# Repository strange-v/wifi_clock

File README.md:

# WiFi Clock
One more WiFi clock based on DS1339U and ESP8266. Requires 12V 1.5A power source.

## Functionality
* 24 hours time format
* Automatic time sync (NTP server and interval can be configured)
* Auto brightness
* DST support
* Display options (on/off leading zero, on/off column blinking, do not blink in a specific period of time)
* Over-the-Air update

## Main components
- ESP8266 - microcontroller 
- DS1339U - real time clock
- PCA9685 x 2 - LED controller
- BH1750FVI-TR - light sensor
- MT2492 - step-down  converter
- LM1117IMP-3.3 - voltage regulator

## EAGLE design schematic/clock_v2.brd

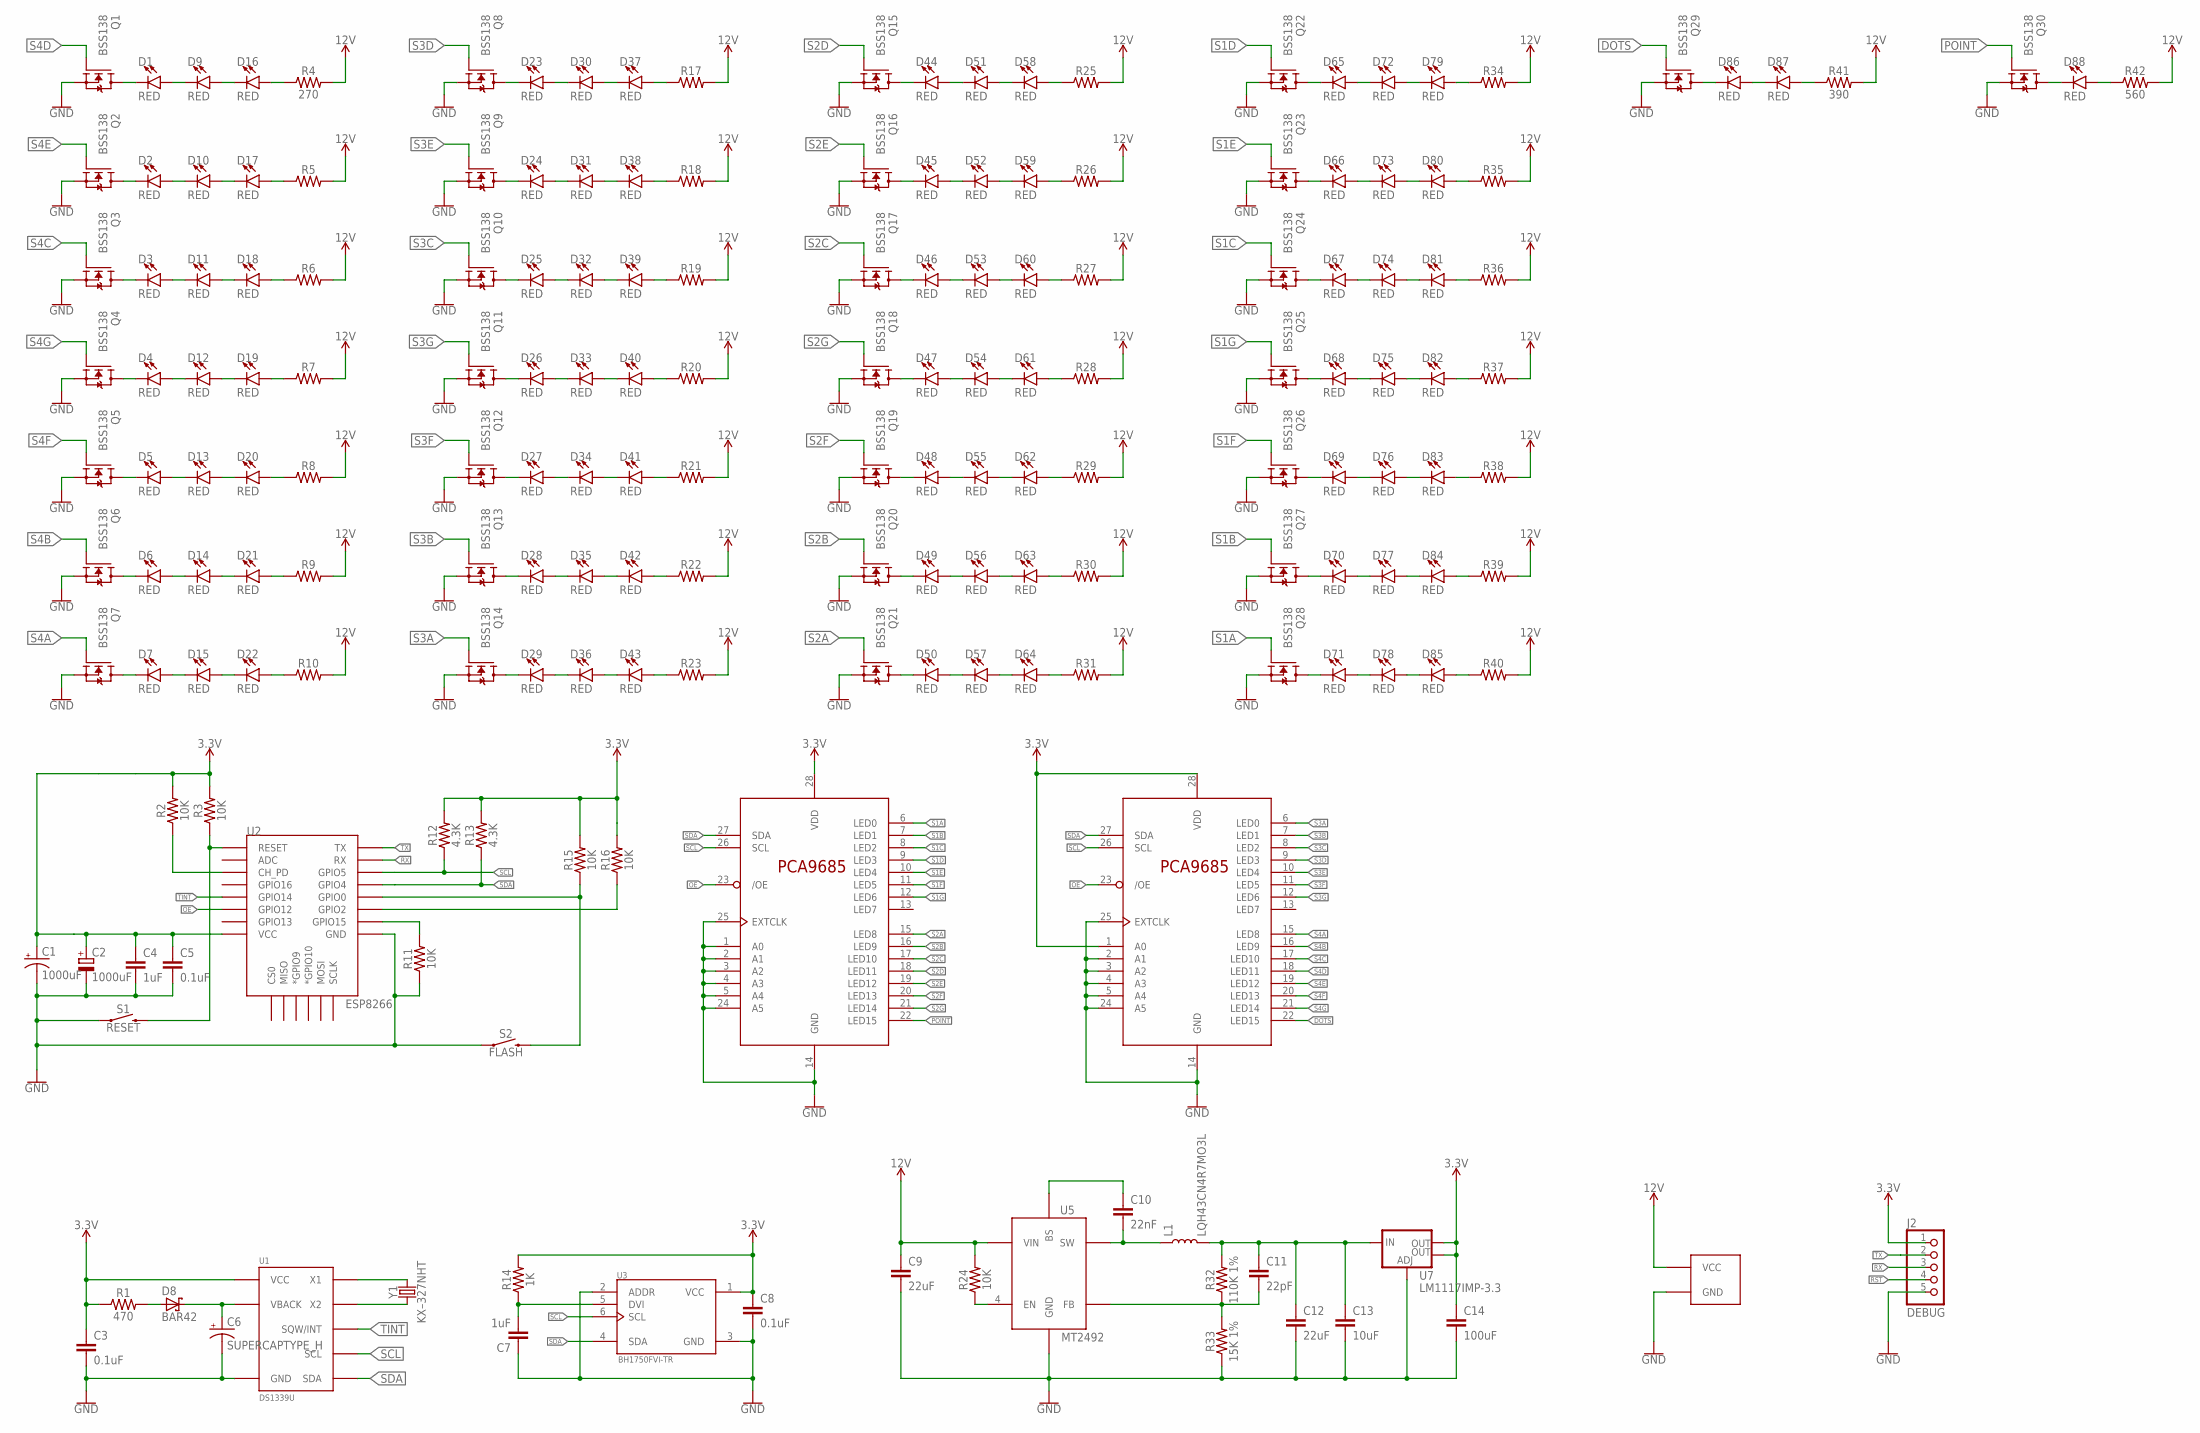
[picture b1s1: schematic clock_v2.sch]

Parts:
C1: 1000uF; CAP_8X11.5_P-3.5
C2: 1000uF; D/7343-31R
C3, C5, C8: 0.1uF; 1206
C4, C7: 1uF; 1206
C6: SUPERCAPTYPE_H; IONISTOR_TYPE_H
C9, C12: 22uF; 1206
C10: 22nF; 1206
C11: 22pF; 1206
C13: 10uF; 1206
C14: 100uF; C/6032-28R
D1, D2, D3, D4, D5, D6, D7, D9, D10, D11, D12, D13, D14, D15, D16, D17, D18, D19, D20, D21, D22, D23, D24, D25, D26, D27, D28, D29, D30, D31, D32, D33, D34, D35, D36, D37, D38, D39, D40, D41, D42, D43, D44, D45, D46, D47, D48, D49, D50, D51, D52, D53, D54, D55, D56, D57, D58, D59, D60, D61, D62, D63, D64, D65, D66, D67, D68, D69, D70, D71, D72, D73, D74, D75, D76, D77, D78, D79, D80, D81, D82, D83, D84, D85, D86, D87, D88: RED; LED-1206
D8: BAR42; SOT23
J1: POWER_SMD5.08; POWER_SMD_5.08
J2: DEBUG; ESP8266_DEBUG
L1: LQH43CN4R7MO3L; C1812
Q1, Q2, Q3, Q4, Q5, Q6, Q7, Q8, Q9, Q10, Q11, Q12, Q13, Q14, Q15, Q16, Q17, Q18, Q19, Q20, Q21, Q22, Q23, Q24, Q25, Q26, Q27, Q28, Q29, Q30: BSS138; SOT23
R1: 470; 1206
R2, R3, R11, R15, R16, R24: 10K; 1206
R4: 270; 1206
R5, R6, R7, R8, R9, R10, R17, R18, R19, R20, R21, R22, R23, R25, R26, R27, R28, R29, R30, R31, R34, R35, R36, R37, R38, R39, R40: 1206
R12, R13: 4.3K; 1206
R14: 1K; 1206
R32: 110K 1%; 1206
R33: 15K 1%; 1206
R41: 390; 1206
R42: 560; 1206
S1: RESET; TACTILE_SWITCH_SMD_5.2MM
S2: FLASH; TACTILE_SWITCH_SMD_5.2MM
U1: DS1339U
U2: ESP8266; ESP12E-SMD
U3: BH1750FVI-TR; SOTFL50P300X75-6N
U4, U6: PCA9685PW; TSSOP28
U5: MT2492; SOT23-6
U7: LM1117IMP-3.3; SOT223
Y1: KX–327NHT; QSMD3.2X1.5

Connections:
3.3V: C1.+, C2.+, C3.1, C4.1, C5.1, C8.1, C14.+ (1), J2.1, R1.1, R2.2, R3.2, R12.2, R13.2, R14.2, R15.2, R16.2, U1.8 (VCC), U2.VCC, U3.1 (VCC), U4.28 (VDD), U6.1 (A0), U6.28 (VDD), U7.2 (OUT), U7.4 (OUT)
12V: C9.1, J1.VCC, R4.2, R5.2, R6.2, R7.2, R8.2, R9.2, R10.2, R17.2, R18.2, R19.2, R20.2, R21.2, R22.2, R23.2, R24.2, R25.2, R26.2, R27.2, R28.2, R29.2, R30.2, R31.2, R34.2, R35.2, R36.2, R37.2, R38.2, R39.2, R40.2, R41.2, R42.2, U5.5 (VIN)
DOTS: Q29.1 (G), U6.22 (LED15)
FLASH: R15.1, S2.3 (2), S2.4 (2), U2.GPIO0
GND: C1.-, C2.-, C3.2, C4.2, C5.2, C6.GND (-), C7.1, C8.2, C9.2, C12.2, C13.2, C14.- (2), J1.GND, J2.5, Q1.2 (S), Q2.2 (S), Q3.2 (S), Q4.2 (S), Q5.2 (S), Q6.2 (S), Q7.2 (S), Q8.2 (S), Q9.2 (S), Q10.2 (S), Q11.2 (S), Q12.2 (S), Q13.2 (S), Q14.2 (S), Q15.2 (S), Q16.2 (S), Q17.2 (S), Q18.2 (S), Q19.2 (S), Q20.2 (S), Q21.2 (S), Q22.2 (S), Q23.2 (S), Q24.2 (S), Q25.2 (S), Q26.2 (S), Q27.2 (S), Q28.2 (S), Q29.2 (S), Q30.2 (S), R11.1, R33.1, S1.1, S1.2 (1), S2.1, S2.2 (1), U1.4 (GND), U2.GND, U3.2 (ADDR), U3.3 (GND), U4.1 (A0), U4.2 (A1), U4.3 (A2), U4.4 (A3), U4.5 (A4), U4.14 (GND), U4.24 (A5), U4.25 (EXTCLK), U5.2 (GND), U6.2 (A1), U6.3 (A2), U6.4 (A3), U6.5 (A4), U6.14 (GND), U6.24 (A5), U6.25 (EXTCLK), U7.1 (ADJ)
unnamed: D1.C, Q1.3 (D)
unnamed: D1.A, D9.C
unnamed: D2.C, Q2.3 (D)
unnamed: D2.A, D10.C
unnamed: D3.C, Q3.3 (D)
unnamed: D3.A, D11.C
unnamed: D11.A, D18.C
unnamed: D18.A, R6.1
unnamed: D4.C, Q4.3 (D)
unnamed: D4.A, D12.C
unnamed: D12.A, D19.C
unnamed: D19.A, R7.1
unnamed: D7.C, Q7.3 (D)
unnamed: D7.A, D15.C
unnamed: D50.C, Q21.3 (D)
unnamed: D23.C, Q8.3 (D)
unnamed: D23.A, D30.C
unnamed: D30.A, D37.C
unnamed: D37.A, R17.1
unnamed: D24.C, Q9.3 (D)
unnamed: D24.A, D31.C
unnamed: D31.A, D38.C
unnamed: D38.A, R18.1
unnamed: D25.C, Q10.3 (D)
unnamed: D25.A, D32.C
unnamed: D32.A, D39.C
unnamed: D39.A, R19.1
unnamed: D27.C, Q12.3 (D)
unnamed: D50.A, D57.C
unnamed: D57.A, D64.C
unnamed: D49.C, Q20.3 (D)
unnamed: D49.A, D56.C
unnamed: D56.A, D63.C
unnamed: D48.C, Q19.3 (D)
unnamed: D48.A, D55.C
unnamed: D55.A, D62.C
unnamed: D47.C, Q18.3 (D)
unnamed: D47.A, D54.C
unnamed: D54.A, D61.C
unnamed: D46.C, Q17.3 (D)
unnamed: D46.A, D53.C
unnamed: D53.A, D60.C
unnamed: D44.C, Q15.3 (D)
unnamed: D44.A, D51.C
unnamed: D51.A, D58.C
unnamed: D52.A, D59.C
unnamed: D45.A, D52.C
unnamed: D45.C, Q16.3 (D)
unnamed: D64.A, R31.1
unnamed: D63.A, R30.1
unnamed: D62.A, R29.1
unnamed: D61.A, R28.1
unnamed: D60.A, R27.1
unnamed: D59.A, R26.1
unnamed: D58.A, R25.1
unnamed: D65.C, Q22.3 (D)
unnamed: D86.A, D87.C
unnamed: D86.C, Q29.3 (D)
unnamed: D9.A, D16.C
unnamed: D16.A, R4.1
unnamed: D10.A, D17.C
unnamed: D17.A, R5.1
unnamed: D15.A, D22.C
unnamed: D22.A, R10.1
unnamed: D6.C, Q6.3 (D)
unnamed: D6.A, D14.C
unnamed: D14.A, D21.C
unnamed: D21.A, R9.1
unnamed: D5.C, Q5.3 (D)
unnamed: D5.A, D13.C
unnamed: D13.A, D20.C
unnamed: D20.A, R8.1
unnamed: D88.C, Q30.3 (D)
unnamed: D27.A, D34.C
unnamed: D87.A, R41.1
unnamed: D88.A, R42.1
unnamed: D34.A, D41.C
unnamed: D41.A, R21.1
unnamed: D28.C, Q13.3 (D)
unnamed: D28.A, D35.C
unnamed: D35.A, D42.C
unnamed: D42.A, R22.1
unnamed: D29.C, Q14.3 (D)
unnamed: D29.A, D36.C
unnamed: D36.A, D43.C
unnamed: D43.A, R23.1
unnamed: D26.C, Q11.3 (D)
unnamed: D26.A, D33.C
unnamed: D33.A, D40.C
unnamed: D40.A, R20.1
unnamed: D65.A, D72.C
unnamed: D72.A, D79.C
unnamed: D79.A, R34.1
unnamed: D66.C, Q23.3 (D)
unnamed: D66.A, D73.C
unnamed: D73.A, D80.C
unnamed: D80.A, R35.1
unnamed: D67.C, Q24.3 (D)
unnamed: D67.A, D74.C
unnamed: D74.A, D81.C
unnamed: D81.A, R36.1
unnamed: D82.A, R37.1
unnamed: D75.A, D82.C
unnamed: D68.A, D75.C
unnamed: D68.C, Q25.3 (D)
unnamed: D69.C, Q26.3 (D)
unnamed: D69.A, D76.C
unnamed: D76.A, D83.C
unnamed: D83.A, R38.1
unnamed: D84.A, R39.1
unnamed: D77.A, D84.C
unnamed: D70.A, D77.C
unnamed: D70.C, Q27.3 (D)
unnamed: D71.C, Q28.3 (D)
unnamed: D71.A, D78.C
unnamed: D78.A, D85.C
unnamed: D85.A, R40.1
unnamed: C6.VCC (+), D8.3 (C), U1.3 (VBACK)
unnamed: C7.2, R14.1, U3.5 (DVI)
unnamed: D8.1 (A), R1.2
unnamed: U1.1 (X1), Y1.2
unnamed: U1.2 (X2), Y1.1
unnamed: R11.2, U2.GPIO15
unnamed: R2.1, U2.CH_PD
unnamed: R16.1, U2.GPIO2
unnamed: R24.1, U5.4 (EN)
unnamed: C10.1, U5.1 (BS)
unnamed: C10.2, L1.1, U5.6 (SW)
unnamed: C11.1, C12.1, C13.1, L1.2, R32.2, U7.3 (IN)
unnamed: C11.2, R32.1, R33.2, U5.3 (FB)
OE: U2.GPIO12, U4.23 (/OE), U6.23 (/OE)
POINT: Q30.1 (G), U4.22 (LED15)
RST: J2.4, R3.1, S1.3 (2), S1.4 (2), U2.RESET
RX: J2.3, U2.RXD0 (RX)
S1A: Q28.1 (G), U4.6 (LED0)
S1B: Q27.1 (G), U4.7 (LED1)
S1C: Q24.1 (G), U4.8 (LED2)
S1D: Q22.1 (G), U4.9 (LED3)
S1E: Q23.1 (G), U4.10 (LED4)
S1F: Q26.1 (G), U4.11 (LED5)
S1G: Q25.1 (G), U4.12 (LED6)
S2A: Q21.1 (G), U4.15 (LED8)
S2B: Q20.1 (G), U4.16 (LED9)
S2C: Q17.1 (G), U4.17 (LED10)
S2D: Q15.1 (G), U4.18 (LED11)
S2E: Q16.1 (G), U4.19 (LED12)
S2F: Q19.1 (G), U4.20 (LED13)
S2G: Q18.1 (G), U4.21 (LED14)
S3A: Q14.1 (G), U6.6 (LED0)
S3B: Q13.1 (G), U6.7 (LED1)
S3C: Q10.1 (G), U6.8 (LED2)
S3D: Q8.1 (G), U6.9 (LED3)
S3E: Q9.1 (G), U6.10 (LED4)
S3F: Q12.1 (G), U6.11 (LED5)
S3G: Q11.1 (G), U6.12 (LED6)
S4A: Q7.1 (G), U6.15 (LED8)
S4B: Q6.1 (G), U6.16 (LED9)
S4C: Q3.1 (G), U6.17 (LED10)
S4D: Q1.1 (G), U6.18 (LED11)
S4E: Q2.1 (G), U6.19 (LED12)
S4F: Q5.1 (G), U6.20 (LED13)
S4G: Q4.1 (G), U6.21 (LED14)
SCL: R12.1, U1.6 (SCL), U2.GPIO5, U3.6 (SCL), U4.26 (SCL), U6.26 (SCL)
SDA: R13.1, U1.5 (SDA), U2.GPIO4, U3.4 (SDA), U4.27 (SDA), U6.27 (SDA)
TINT: U1.7 (SQW/INT), U2.GPIO14
TX: J2.2, U2.TXD0 (TX)

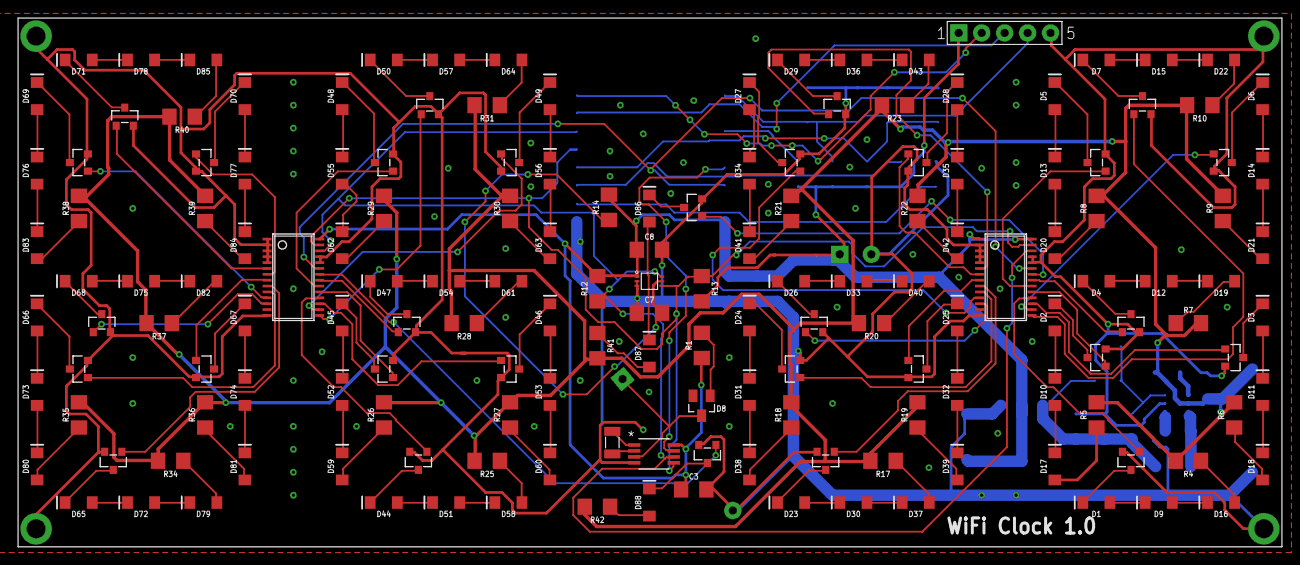
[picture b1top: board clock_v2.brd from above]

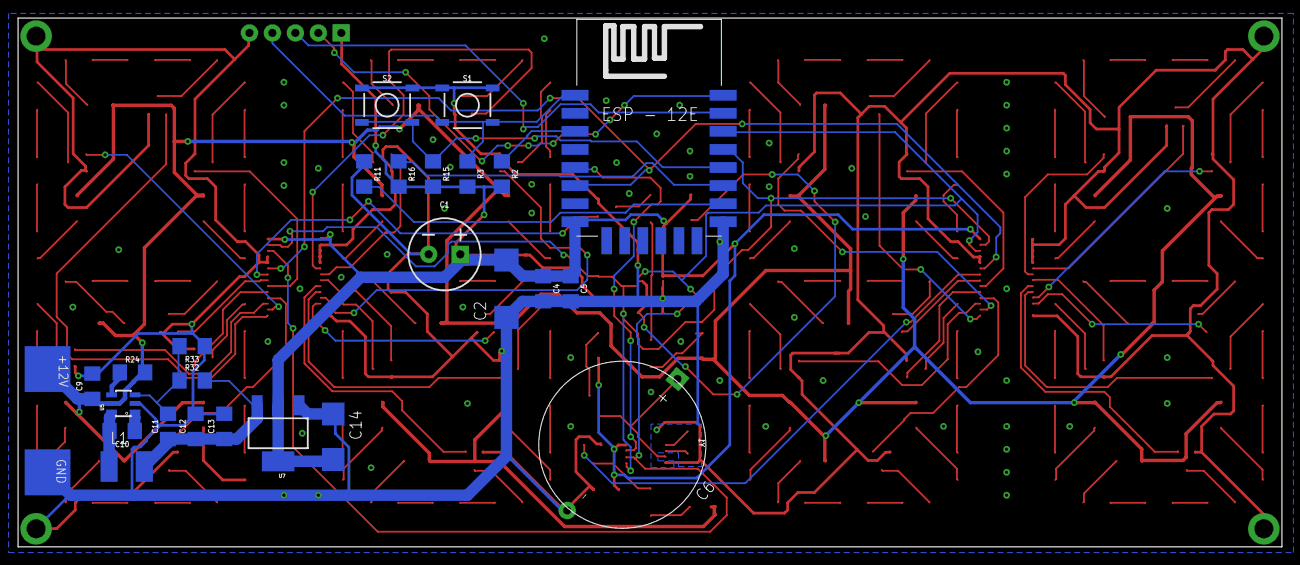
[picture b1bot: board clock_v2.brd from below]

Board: 2 copper layers, 139.9 x 58.5 mm, 187 parts (26 on the bottom side), 171 nets.

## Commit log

2018-10-14 Created project, added settings functionality
2018-10-15 Added network functionality (connect, start AP, etc)
2018-10-15 Improved Network functions, introduced Led class, TimeSync functionality
2018-10-16 Fixed time sync issue, added time displaying, timezones
2018-10-17 Use different RTC class, refactoring
2018-10-17 Improved settings to store TimeChangeRule
2018-10-17 Fixed incorrect date
2018-10-17 Fixed incorrect time displaying (zero related), refactoring
2018-10-17 Added do not blink functionality
2018-10-17 Added dummy brightness control
2018-10-18 Moved SimpleTime struct to a separate file, fixed overload methods
2018-10-18 Added operators + and - for SimpleTime, improved do not blink period calculation for column
2018-10-20 Added web server functionality, refactored: - SimpleTime - added loading and displaying wifi SSID - Led class
2018-10-21 Integrated simple lux to PWM mapping Fixed bug in SettingsHelper Improved API path
2018-10-21 Implemented save settings functionality, improved SettingsHelper
2018-10-21 Moved UTC -> local conversion to display functionality
2018-10-29 Improved JSON parsing, fixed time bug
2019-01-02 Added web app files, initialized time sync
2019-01-06 Added schematic, updated readme
2020-03-14 Changed structure (migration to PIO)
2020-03-14 Implemented correct offset support Bug-fix: Start web server after AP initialized. Migrated project to PIO. Updated UI files.
2020-10-07 Moved project to PIO, fixed incorrect start with no WiFi

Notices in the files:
parts and their libraries:
SparkFun-LED: Licensing: Creative Commons ShareAlike 4.0 International - https://creativecommons.org/licenses/by-sa/4.0
